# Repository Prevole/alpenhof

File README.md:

# Maquette Alpenhof

A model railway lighting project featuring individually controlled LED lighting for buildings and scenery.

## Architecture

- **Controller:** Raspberry Pi Pico 2 WH generates control signals.
- **LED Drivers:** ULN2803A ICs switch each LED independently on the ground side.
- **LED Hub:** Custom KiCad PCB distributes power and connects up to 16 LEDs via JST-XH connectors.
- **Power:** External 15V DC supply powers the LEDs independently of the Pico.
- **Interconnection:** A 20-pin IDC ribbon cable carries 16 individual LED channels and four shared +15V connections between the controller and hub.

The Pico controls the drivers; it does not supply power directly to the LEDs. All circuits share a common ground.

## Status

Work in progress.

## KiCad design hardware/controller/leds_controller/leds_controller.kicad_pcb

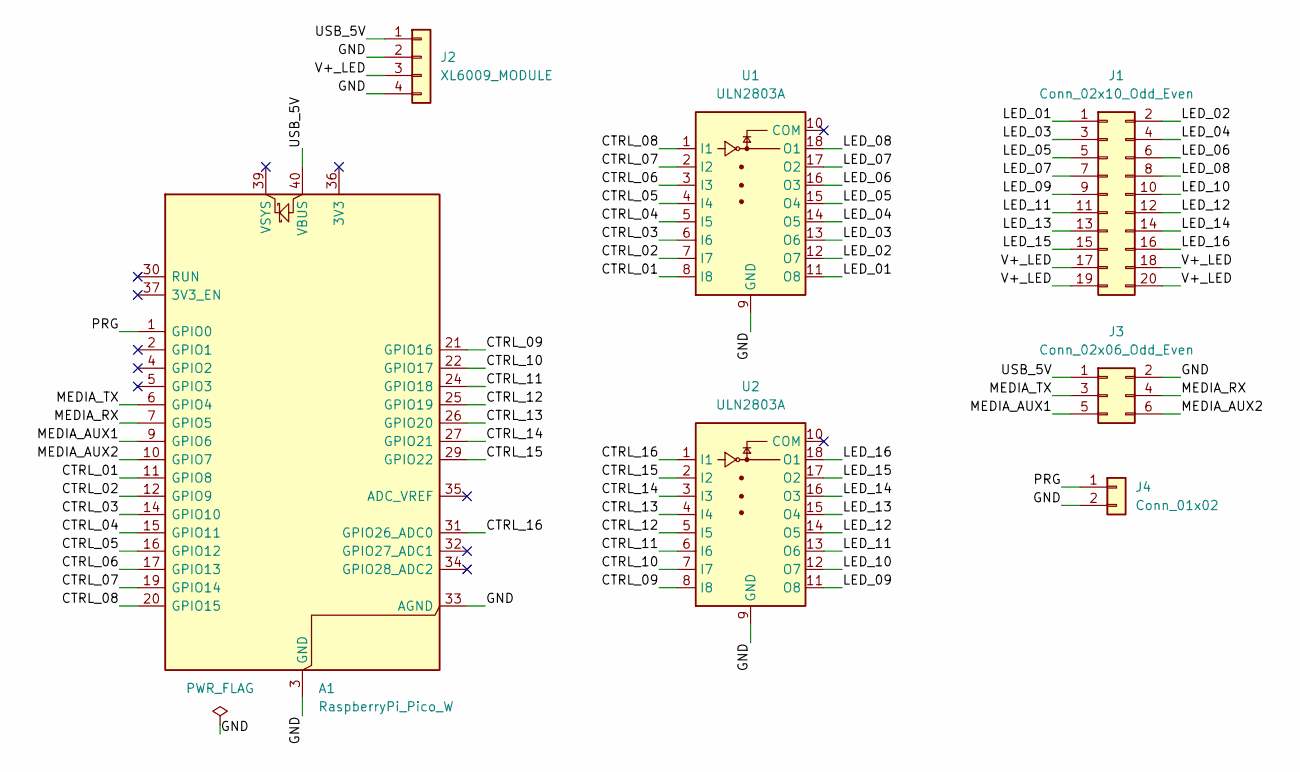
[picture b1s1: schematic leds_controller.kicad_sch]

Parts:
A1: RaspberryPi_Pico_W; RaspberryPi_Pico_Common_Unspecified
J1: Conn_02x10_Odd_Even; IDC-Header_2x10_P2.54mm_Vertical
J2: XL6009_MODULE; XL6009_Module_Socket
J3: Conn_02x06_Odd_Even; IDC-Header_2x03_P2.54mm_Vertical
J4: Conn_01x02; JST_XH_B2B-XH-A_1x02_P2.50mm_Vertical
U1, U2: ULN2803A; DIP-18_W7.62mm_Socket

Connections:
/CTRL_01: A1.11 (GPIO8), U1.8 (I8)
/CTRL_02: A1.12 (GPIO9), U1.7 (I7)
/CTRL_03: A1.14 (GPIO10), U1.6 (I6)
/CTRL_04: A1.15 (GPIO11), U1.5 (I5)
/CTRL_05: A1.16 (GPIO12), U1.4 (I4)
/CTRL_06: A1.17 (GPIO13), U1.3 (I3)
/CTRL_07: A1.19 (GPIO14), U1.2 (I2)
/CTRL_08: A1.20 (GPIO15), U1.1 (I1)
/CTRL_09: A1.21 (GPIO16), U2.8 (I8)
/CTRL_10: A1.22 (GPIO17), U2.7 (I7)
/CTRL_11: A1.24 (GPIO18), U2.6 (I6)
/CTRL_12: A1.25 (GPIO19), U2.5 (I5)
/CTRL_13: A1.26 (GPIO20), U2.4 (I4)
/CTRL_14: A1.27 (GPIO21), U2.3 (I3)
/CTRL_15: A1.29 (GPIO22), U2.2 (I2)
/CTRL_16: A1.31 (GPIO26_ADC0), U2.1 (I1)
/GND: A1.3 (GND), A1.8 (GND), A1.13 (GND), A1.18 (GND), A1.23 (GND), A1.28 (GND), A1.33 (AGND), A1.38 (GND), J2.2, J2.4, J3.2, J4.2, U1.9 (GND), U2.9 (GND)
/LED_01: J1.1, U1.11 (O8)
/LED_02: J1.2, U1.12 (O7)
/LED_03: J1.3, U1.13 (O6)
/LED_04: J1.4, U1.14 (O5)
/LED_05: J1.5, U1.15 (O4)
/LED_06: J1.6, U1.16 (O3)
/LED_07: J1.7, U1.17 (O2)
/LED_08: J1.8, U1.18 (O1)
/LED_09: J1.9, U2.11 (O8)
/LED_10: J1.10, U2.12 (O7)
/LED_11: J1.11, U2.13 (O6)
/LED_12: J1.12, U2.14 (O5)
/LED_13: J1.13, U2.15 (O4)
/LED_14: J1.14, U2.16 (O3)
/LED_15: J1.15, U2.17 (O2)
/LED_16: J1.16, U2.18 (O1)
/MEDIA_AUX1: A1.9 (GPIO6), J3.5
/MEDIA_AUX2: A1.10 (GPIO7), J3.6
/MEDIA_RX: A1.7 (GPIO5), J3.4
/MEDIA_TX: A1.6 (GPIO4), J3.3
/PRG: A1.1 (GPIO0), J4.1
/USB_5V: A1.40 (VBUS), J2.1, J3.1
/V+_LED: J1.17, J1.18, J1.19, J1.20, J2.3

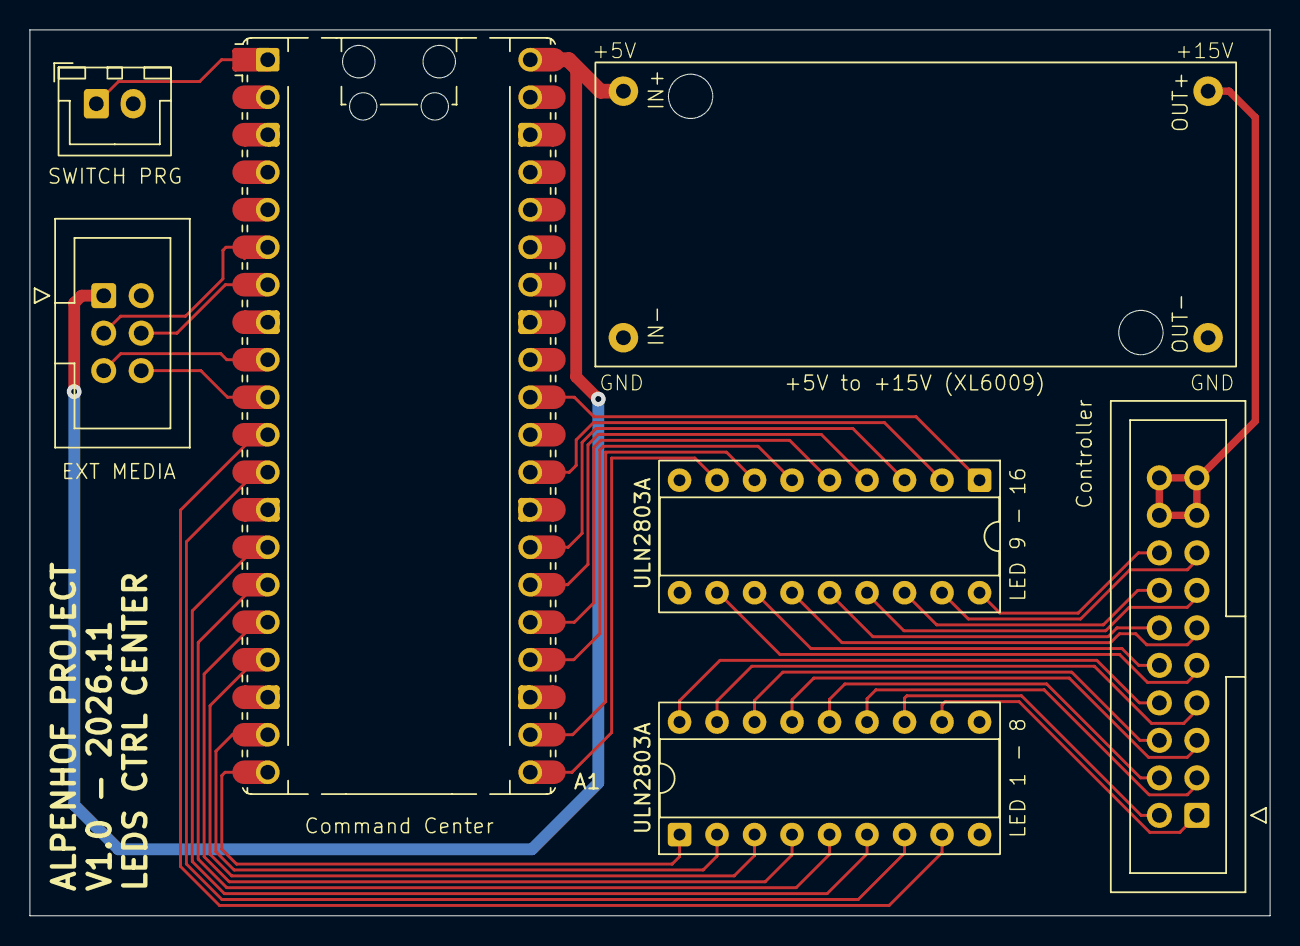
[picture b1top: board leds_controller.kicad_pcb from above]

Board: 2 copper layers, 84.0 x 60.0 mm, 7 parts (0 on the bottom side), 40 nets.

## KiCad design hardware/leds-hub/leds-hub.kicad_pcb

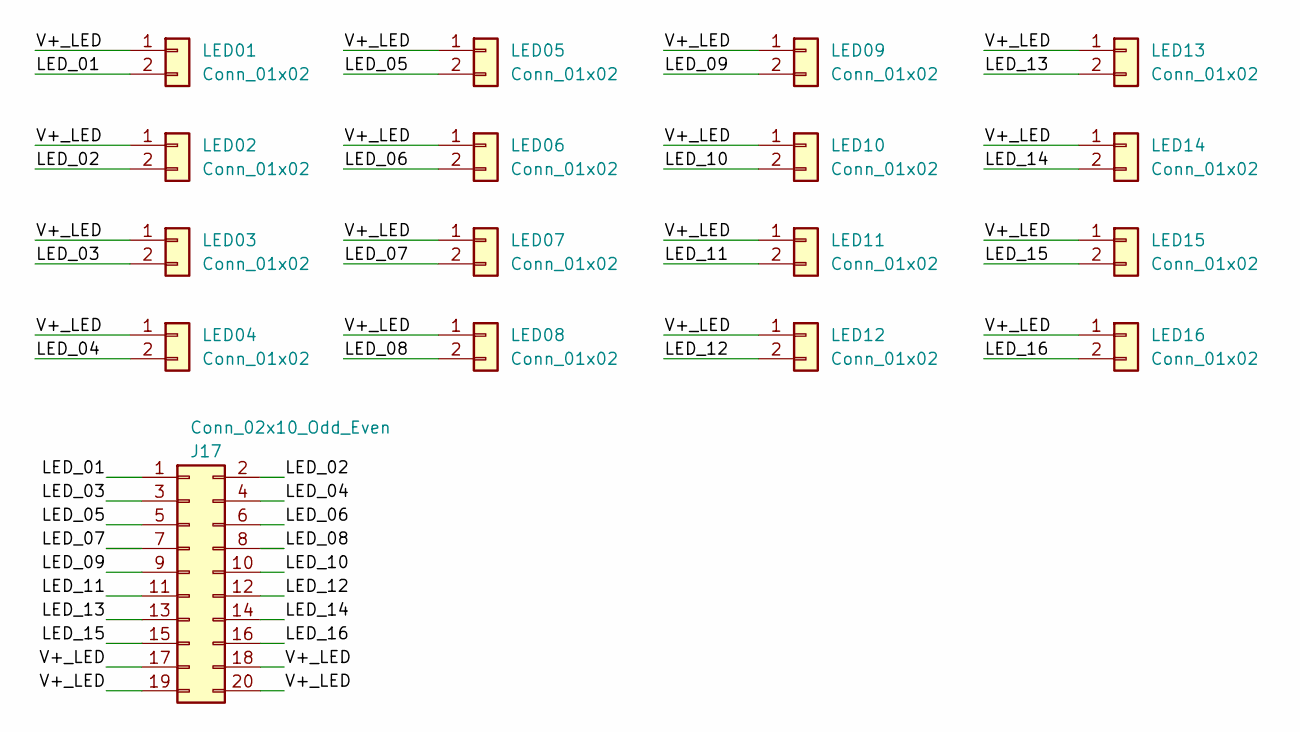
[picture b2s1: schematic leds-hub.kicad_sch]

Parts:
J17: Conn_02x10_Odd_Even; IDC-Header_2x10_P2.54mm_Vertical
LED01, LED02, LED03, LED04, LED05, LED06, LED07, LED08, LED09, LED10, LED11, LED12, LED13, LED14, LED15, LED16: Conn_01x02; JST_XH_B2B-XH-A_1x02_P2.50mm_Vertical

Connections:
/LED_01: J17.1, LED01.2
/LED_02: J17.2, LED02.2
/LED_03: J17.3, LED03.2
/LED_04: J17.4, LED04.2
/LED_05: J17.5, LED05.2
/LED_06: J17.6, LED06.2
/LED_07: J17.7, LED07.2
/LED_08: J17.8, LED08.2
/LED_09: J17.9, LED09.2
/LED_10: J17.10, LED10.2
/LED_11: J17.11, LED11.2
/LED_12: J17.12, LED12.2
/LED_13: J17.13, LED13.2
/LED_14: J17.14, LED14.2
/LED_15: J17.15, LED15.2
/LED_16: J17.16, LED16.2
/V+_LED: J17.17, J17.18, J17.19, J17.20, LED01.1, LED02.1, LED03.1, LED04.1, LED05.1, LED06.1, LED07.1, LED08.1, LED09.1, LED10.1, LED11.1, LED12.1, LED13.1, LED14.1, LED15.1, LED16.1

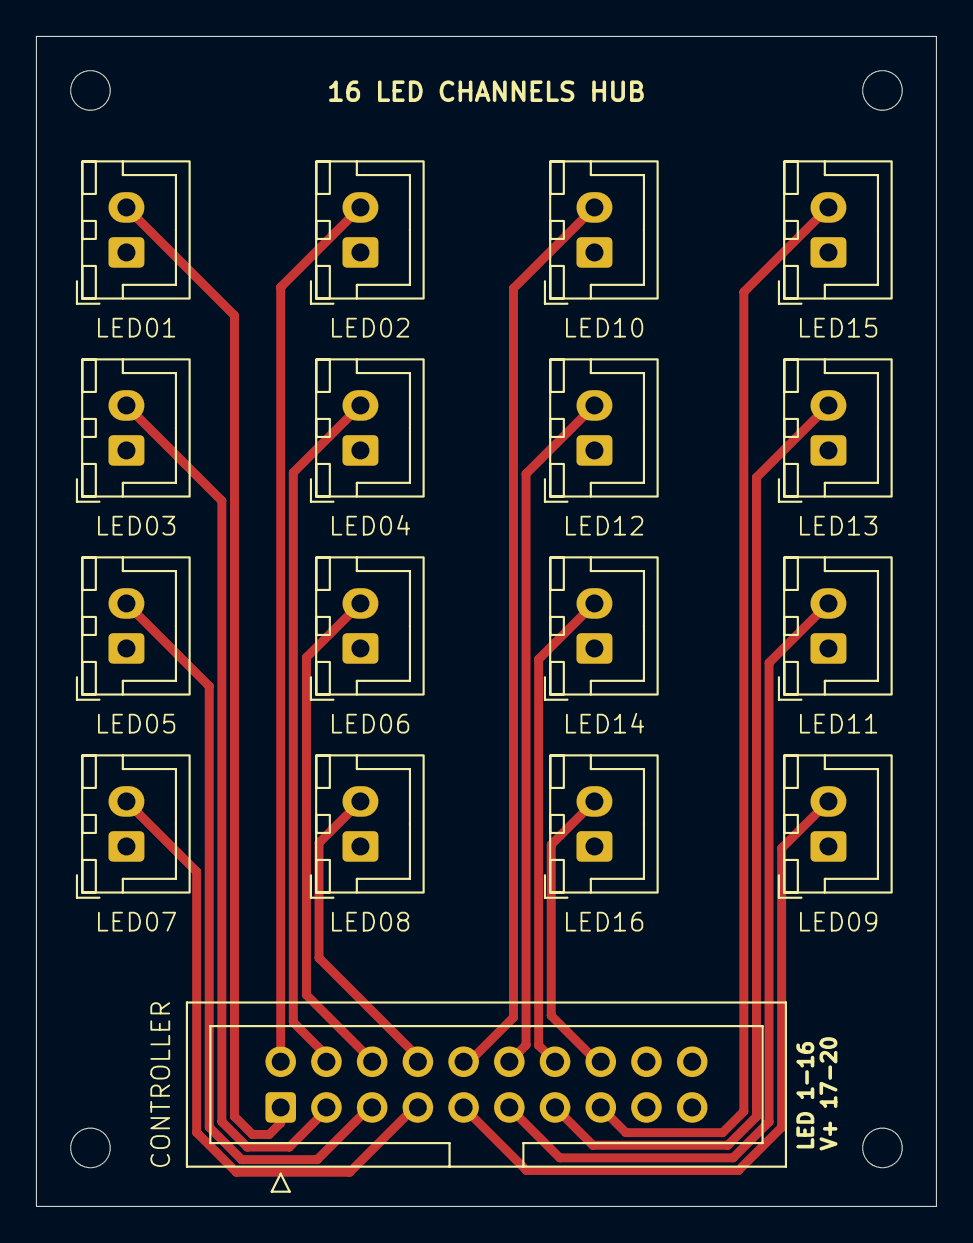
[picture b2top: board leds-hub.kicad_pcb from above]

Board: 2 copper layers, 50.0 x 65.0 mm, 21 parts (0 on the bottom side), 17 nets.

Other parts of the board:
H1, H2, H3, H4: MountingHole_2.2mm_M2
